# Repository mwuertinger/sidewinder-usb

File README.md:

# sidewinder-usb
This repository contains hard- and software for building a USB adapter for the
[MS SideWinder 3D Pro](https://en.wikipedia.org/wiki/Microsoft_SideWinder#3D_Pro) joystick.

The joystick uses a proprietary protocol over the analg gameport which makes it impossible to use
standard off the shelf gameport USB adapters. The protocol works by sending a state vector over the
three button lines of the gameport. There is no analog transmission taking place. More details can
be found in [US patent 5628686A](https://patents.google.com/patent/US5628686A/en) or in the [Linux
driver](https://github.com/torvalds/linux/blob/master/drivers/input/joystick/sidewinder.c)
implementation.

## Software
The software is taken from [sw3dprousb](https://code.google.com/archive/p/sw3dprousb) with
permission from the [author](mailto:detlef@gmail.com). All credit regarding the software goes to the
original author.

The ATmega32u4 controller comes with a pre-configured bootloader which is
[DFU](https://en.wikipedia.org/wiki/USB#Device_Firmware_Upgrade) compatible. This allows to flash
the firmware via USB without the need for an
[ICSP](https://en.wikipedia.org/wiki/In-system_programming) port.

The [flash-firmware.sh](/flash-firmware.sh) script can be used to flash the firmware
on a newly assembled board using the [dfu-programmer](https://dfu-programmer.github.io/) utility.
This should work out of the box on Linux systems provided that there is only one DFU device present.

## Hardware
The hardware is based on a minimal design around the ATmega32u4 microcontroller and follows the
suggestions from the sw3dprousb project as well as from
[this DescentBB thread](https://www.descentbb.net/viewtopic.php?t=15526).

### Schematic

### Board Layout

### Picture of an assembled v0.2 board

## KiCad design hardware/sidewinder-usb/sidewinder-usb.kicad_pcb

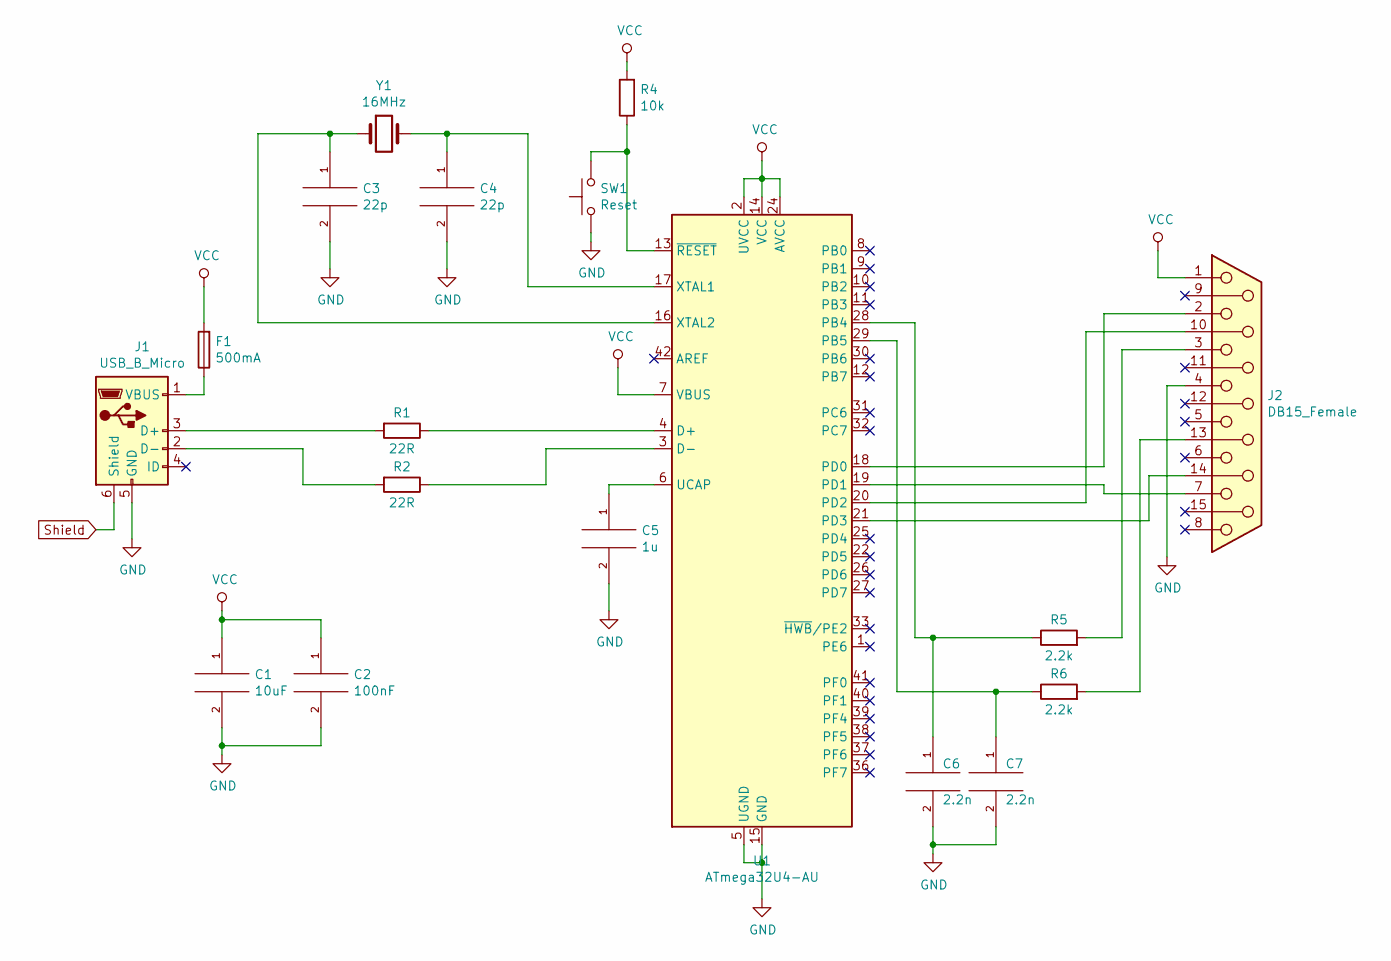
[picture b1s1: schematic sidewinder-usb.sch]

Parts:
C1: 10uF; C_0805_2012Metric
C2: 100nF; C_0805_2012Metric
C3, C4: 22p; C_0805_2012Metric
C5: 1u; C_0805_2012Metric
C6, C7: 2.2n; C_0805_2012Metric
F1: 500mA; Fuse_0805_2012Metric
J1: USB_B_Micro; USB_Micro-B_Molex-105017-0001
J2: DB15_Female; 618015233821
R1, R2: 22R; R_0805_2012Metric
R4: 10k; R_0805_2012Metric
R5, R6: 2.2k; R_0805_2012Metric
SW1: Reset; SW_Push_1P1T_NO_6x6mm_H9.5mm
U1: ATmega32U4-AU; TQFP-44_10x10mm_P0.8mm
Y1: 16MHz; Auris_HC49USSMD

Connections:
GND: C1.2, C2.2, C3.2, C4.2, C5.2, C6.2, C7.2, J1.5 (GND), J2.4, SW1.1, U1.5 (UGND), U1.15 (GND), U1.23 (GND), U1.35 (GND), U1.43 (GND)
unnamed: C3.1, U1.16 (XTAL2), Y1.1
unnamed: C4.1, U1.17 (XTAL1), Y1.2
unnamed: C5.1, U1.6 (UCAP)
unnamed: C6.1, R5.1, U1.28 (PB4)
unnamed: C7.1, R6.1, U1.29 (PB5)
unnamed: F1.1, J1.1 (VBUS)
unnamed: J1.2 (D-), R2.2
unnamed: J1.3 (D+), R1.2
unnamed: J2.2, U1.18 (PD0)
unnamed: J2.3, R5.2
unnamed: J2.7, U1.19 (PD1)
unnamed: J2.10, U1.20 (PD2)
unnamed: J2.13, R6.2
unnamed: J2.14, U1.21 (PD3)
unnamed: R1.1, U1.4 (D+)
unnamed: R2.1, U1.3 (D-)
unnamed: R4.1, SW1.2, U1.13 (~RESET)
Shield: J1.6 (Shield), J2.S1, J2.S2
VCC: C1.1, C2.1, F1.2, J2.1, R4.2, U1.2 (UVCC), U1.7 (VBUS), U1.14 (VCC), U1.24 (AVCC), U1.34 (VCC), U1.44 (AVCC)

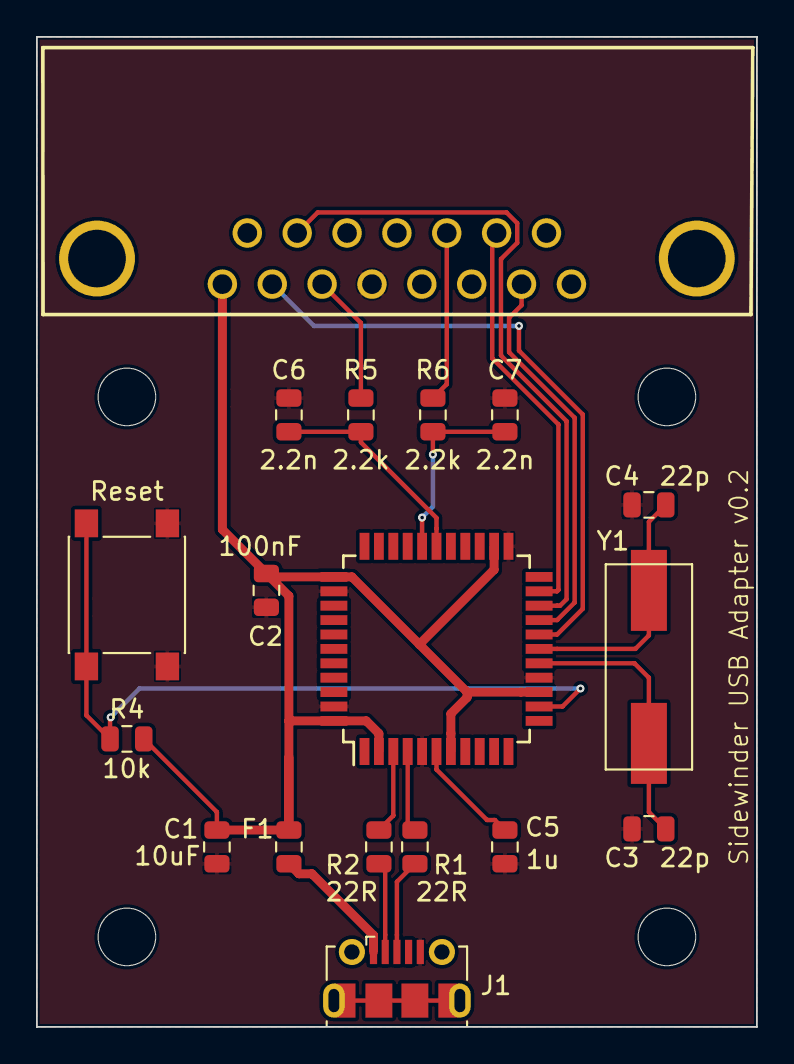
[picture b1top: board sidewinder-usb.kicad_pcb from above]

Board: 2 copper layers, 40.0 x 55.0 mm, 18 parts (0 on the bottom side), 20 nets.

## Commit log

2020-02-29 Initial import
2020-02-29 Tools for installing firmware
2020-03-03 Add a copy of the software
    Software copied from https://code.google.com/archive/p/sw3dprousb/
2020-03-03 Add README and LICENSE
2020-03-03 Fix flash-firmware.sh link
2020-03-03 Embed schematic.png in README.md
2020-03-03 Add board images
2020-03-03 Change flash-firmware.sh link
2020-03-06 KiCad Design
2020-03-06 Final design for v0.2
2020-03-06 Remove old (Target 3001) design
2020-03-06 Clean up folder structure
2020-03-06 Add schematic and board screenshots
2020-03-06 Add picture headlines
2020-09-20 Add XML file and gerber.zip
2020-09-20 Add acryl case design file
2020-09-27 Add erase-firmware.sh
2020-12-31 Replace image of assembled board
2020-12-31 Fix software author email address
